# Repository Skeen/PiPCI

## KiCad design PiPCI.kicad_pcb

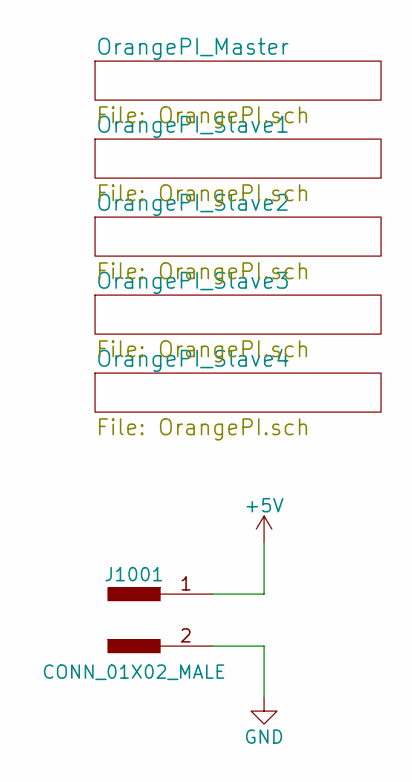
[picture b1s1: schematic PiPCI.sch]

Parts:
J1001: CONN_01X02_MALE; AK300-2

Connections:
+5V: J1001.1; also elsewhere on the board
GND: J1001.2; also elsewhere on the board

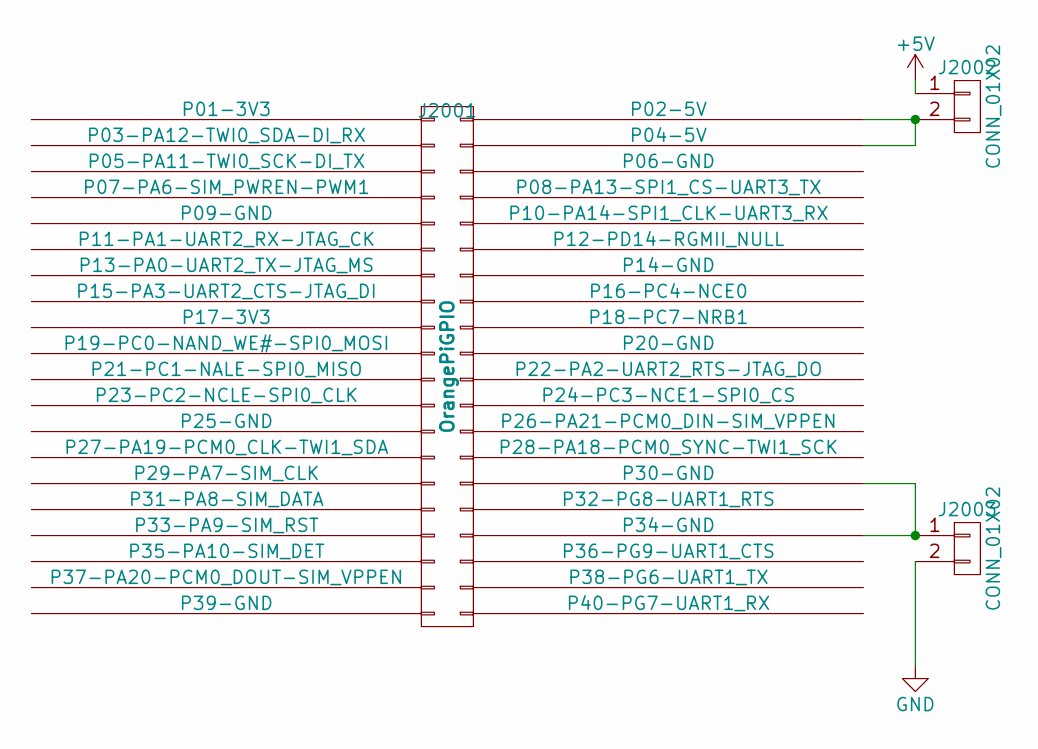
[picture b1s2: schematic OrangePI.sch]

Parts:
J2001: OrangePiGPIO; Socket_Strip_Angled_2x20_Pitch2.54mm
J2002, J2003: CONN_01X02; Pin_Header_Straight_1x02_Pitch2.54mm

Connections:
+5V: J2002.1; also elsewhere on the board
GND: J2003.2; also elsewhere on the board
unnamed: J2001.2 (P02-5V), J2001.4 (P04-5V), J2002.2
unnamed: J2001.30 (P30-GND), J2001.34 (P34-GND), J2003.1

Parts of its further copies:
J3001, J4001, J5001, J6001: OrangePiGPIO; Socket_Strip_Angled_2x20_Pitch2.54mm
J3002, J3003, J4002, J4003, J5002, J5003, J6002, J6003: CONN_01X02; Pin_Header_Straight_1x02_Pitch2.54mm

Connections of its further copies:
+5V: J3002.1, J4002.1, J5002.1, J6002.1; also elsewhere on the board
GND: J3003.2, J4003.2, J5003.2, J6003.2; also elsewhere on the board
unnamed: J3001.2 (P02-5V), J3001.4 (P04-5V), J3002.2
unnamed: J3001.30 (P30-GND), J3001.34 (P34-GND), J3003.1
unnamed: J4001.2 (P02-5V), J4001.4 (P04-5V), J4002.2
unnamed: J4001.30 (P30-GND), J4001.34 (P34-GND), J4003.1
unnamed: J5001.2 (P02-5V), J5001.4 (P04-5V), J5002.2
unnamed: J5001.30 (P30-GND), J5001.34 (P34-GND), J5003.1
unnamed: J6001.2 (P02-5V), J6001.4 (P04-5V), J6002.2
unnamed: J6001.30 (P30-GND), J6001.34 (P34-GND), J6003.1

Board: 2 copper layers, 16 parts (0 on the bottom side), 12 nets, no tracks yet.
